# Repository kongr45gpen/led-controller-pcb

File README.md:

# led-controller-pcb

A PCB to control LEDs (up to 5 channels) using PWM, based on an Espressif ESP32-C6 development board.

Do you want to control your LEDs through Wi-Fi, Bluetooth or Zigbee, but you don't have 100€ lying around? This project is for you!
## Images

## Features

- 5 PWM **output channels**
- 5 **switch MOSFETS** (up to 8A)
- VIN **up to 28V**
- ESP32-C6 controllable through **USB, Wi-Fi, Bluetooth 5 (LE), IEEE 802.15.4**
- Support for RGB, RGBW, RGBWW/CW, WS2812B, and other configurations
- Control through MQTT, HomeAssistant
- **Non**-isolated input
- Fully open-source software and hardware
- 6.25 × 5 cm
- Not battle tested, so might stop working randomly

## Software

You can write your software using any framework you prefer. This board is built and will work out of the box for the [kongr45gpen/ledstripesp32](https://github.com/kongr45gpen/ledstripesp32) project specifically.

## Bill of Materials

This board is meant to function as a **controller** (generating low-power PWM signals from a network/wired input), as a **dimmer** (switching high-power LED lights on/off based on the input signal) or both.

The **controller** function is based on the [ESP32-C6-DevKitC-1](https://docs.espressif.com/projects/espressif-esp-dev-kits/en/latest/esp32c6/esp32-c6-devkitc-1/index.html) development board, but other ESP32 development boards should be also usable (not tested).

The **dimmer** function relies on a few MOSFETs to control the current flow from the output.

The rest of the components are mostly optional and slightly improve the functionality of the board (connectors, pull-down resistors etc). The user can choose whichever components they need and assemble the board to their preference. Many components (e.g. DC barrel jack, headers, passives) may be replaceable with cheaper generic alternatives.

An all-around configuration should cost ~20€, and adding a screen, voltage regulator and detachable headers should move the price up to ~35€.

A total project cost for a simple RGB led control system could be: 5m 5050 12V RGB LED strip (10€) + 12V 1A power supply (10€) + PCB (6€) + components (20€) = 46€.

With example parts and prices from Mouser:

| Ref | Part | Qu.| CONT. | DIM. | Description | Price |
| :-- | :--- | :------: | :--------: | :----: | ----------- | ----: |
| Brd1 | 4-pin I2C SSD1306 | 1 | ❓ | | Debugging info screen | 3€ |
| C1 | C 100nF 0603 (1608 metric) | 1 | | ✔️ | Decoupling capacitor | [0.1€](https://www.mouser.com/ProductDetail/581-04026D104KAT4A) |
| J1 | CUI PJ-063AH | 1 | | ❓ | VIN Barrel connector | [1.5€](https://www.mouser.com/ProductDetail/490-PJ-063AH) |
| J2 | Molex SL 171971-0002 | 1 | | ❓ | VIN Header connector | [0.8€](https://www.mouser.com/ProductDetail/Molex/171971-0002?qs=lc2O%252BfHJPVZiIVvtLkRJ0A%3D%3D) |
| J3 | Molex SL 171971-0007 | 1 | ❓ | ❓ | PWM input/output connector (5 pins + GND) | [1.5€](https://www.mouser.com/ProductDetail/Molex/171971-0007?qs=lc2O%252BfHJPVYTelce0YNW%252BQ%3D%3D) |
| J4 | 5mm 6-pin screw terminal | 1 | | ✔️ | Power output (5 pins + VDD) | [0.9€](https://www.mouser.com/ProductDetail/490-TB003-500-P06BE) |
| J5 | Molex SL 171971-0003 | 1 | ❓ | | Addressable LED output | [1.1€](https://www.mouser.com/ProductDetail/Molex/171971-0003?qs=lc2O%252BfHJPVYq9zLgxhm5jg%3D%3D) |
| LED1..5 | 0805 (2012 metric) LED | 5 | ❓ | ❓ | Indicator LEDs for PWM | [1.25€](https://www.mouser.com/ProductDetail/859-LTST-C170KFKT) |
| LED\_POWER1 | 0805 (2012 metric) LED | 1 | | ❓ | Indicator LED for VDD | [0.25€](https://www.mouser.com/ProductDetail/859-LTST-C170KFKT) |
| Q1..5 | IRLTS6342 (N-MOSFET) | 5 | | ✔️ | Control transistors (use as many as needed) | [1.7€](https://www.mouser.com/ProductDetail/Infineon-Technologies/IRLTS6342TRPBF?qs=8jYDHybYAxsDJhh9ct3B2Q%3D%3D) |
| R1..6 | R 15kΩ 0603 (1608 metric) | 6 | | ❓ | LED series resistors (use as many as needed) | [0.1€](https://www.mouser.com/ProductDetail/603-RC0603FR-0715KL) |
| Rpd1..5 | R 100kΩ 0603 (1608 metric) | 5 | ❓ | ❓ | Pull-down resistors to keep output off when disconnected | [0.1€](https://www.mouser.com/ProductDetail/603-RC0402FR-07100KL) |
| SW1 | PTS647SM70SMTR2LFS | 1 | ❓ | | ESP32 input switch | [0.2€](https://www.mouser.com/ProductDetail/CK/PTS647SM70SMTR2LFS?qs=PqoDHHvF64%252Bxl5nIb9IaOw%3D%3D) |
| U1 | ESP32-C6-DevKitC-1 | 1 | ✔️ | | ESP32 development kit | [8€](https://www.mouser.com/ProductDetail/356-ESP32C6DKC1N8) |
| VR1 | Wurth 1769405241 | 1 | ❓ | | Voltage regulator to provide 5V to ESP32 from VIN | [5€](https://www.mouser.com/ProductDetail/710-1769405241) |

### Extra Accessories

| Part | Quantity | CONTROLLER | DIMMER | Description | Price |
|---|:---:|:---:|:---:|---|---:|
| 4-pin header | 1 | ❓ |  | For screen (`Brd1`) | [0.7€](https://www.mouser.com/ProductDetail/200-CES10402TS) |
| 16-pin-header | 2 | ❓ | | For ESP32 (`U1`) | [5€](https://www.mouser.com/ProductDetail/200-CES11601TS) |
| Molex 14-60-0024 | 1 | | ❓ | Wire plug for `J2` | [0.4€](https://www.mouser.com/ProductDetail/538-14-60-0024) |
| Molex 14-60-0072 | 1 | ❓ | ❓ | Wire plug for `J3` | [1.5€](https://www.mouser.com/ProductDetail/538-14-60-0072) |
| Molex 14-56-7032 | 1 | ❓ | | Wire plug for `J5` | [0.7€](https://www.mouser.com/ProductDetail/538-14-56-7032) |

### Solder Bridges

Some solder bridges/solder jumpers may need to be soldered before any operation can take place.

| Ref | Pins | CONTROLLER | DIMMER | Description |
| :-- | :--: | :--------: | :----: | :---------- |
| JP1 | 3    |            | ✔️     | Controls the source of `VDD` for the LED power output. Bridge 2-1 to connect to `5V`. Bridge 2-3 to connect to `VIN` (J1, J2). |
| JP2 | 3    | ❓          |       | Controls the voltage source (typically 5V) for the addressable strip. Bridge 2-1 to connect to `5V`. Bridge 2-3 to connect to `VIN` (J1, J2). |
| JP3 | 2    |           | ✔️       | Bridge to connect power ground with digital ground. **Must** solder for proper operation.  |
| JP4 | 2    | ❓          |         | Bridge to connect VR1 output to 5V. Must solder to enable voltage regulation from VIN to ESP32 5V. Keep desoldered during debugging to prevent damaging your equipment.  |
| JPout1..5 | 2 | | ✔️ | Bridge to connect transistor outputs to output connector. You can alternatively wire a series resistor here for your output, if needed. |

### Example configurations

**All-in-one controller, from Wi-Fi to RGB LED strip**:
- C1, J1 to connect an external 12V power supply
- VR1 to convert the external 12V to 5V for the ESP32
- LED1..3, LED_POWER1, R1..3, R6 for debugging indicators
- Q1..3 as amplifiers
- Rpd1..3 to prevent lights from going up during boot
- J4 to screw LED strip wires
- U1 for control
- Bridge JP1 (2-3), JP3, JPout1..3. After uploading code, bridge JP4.
- BOM cost: **18€**

**Addressable strip controller with debugging screen**:
- No need for power input, as the ESP32 dev board already has USB-C connections
- U1 for control
- J5 connector to output addressable LED data
- J5 wire plug to solder on addressable LED
- Brd1 screen + 4-pin header to allow detaching it
- Bridge JP2 (2-1)
- BOM cost: **6€**

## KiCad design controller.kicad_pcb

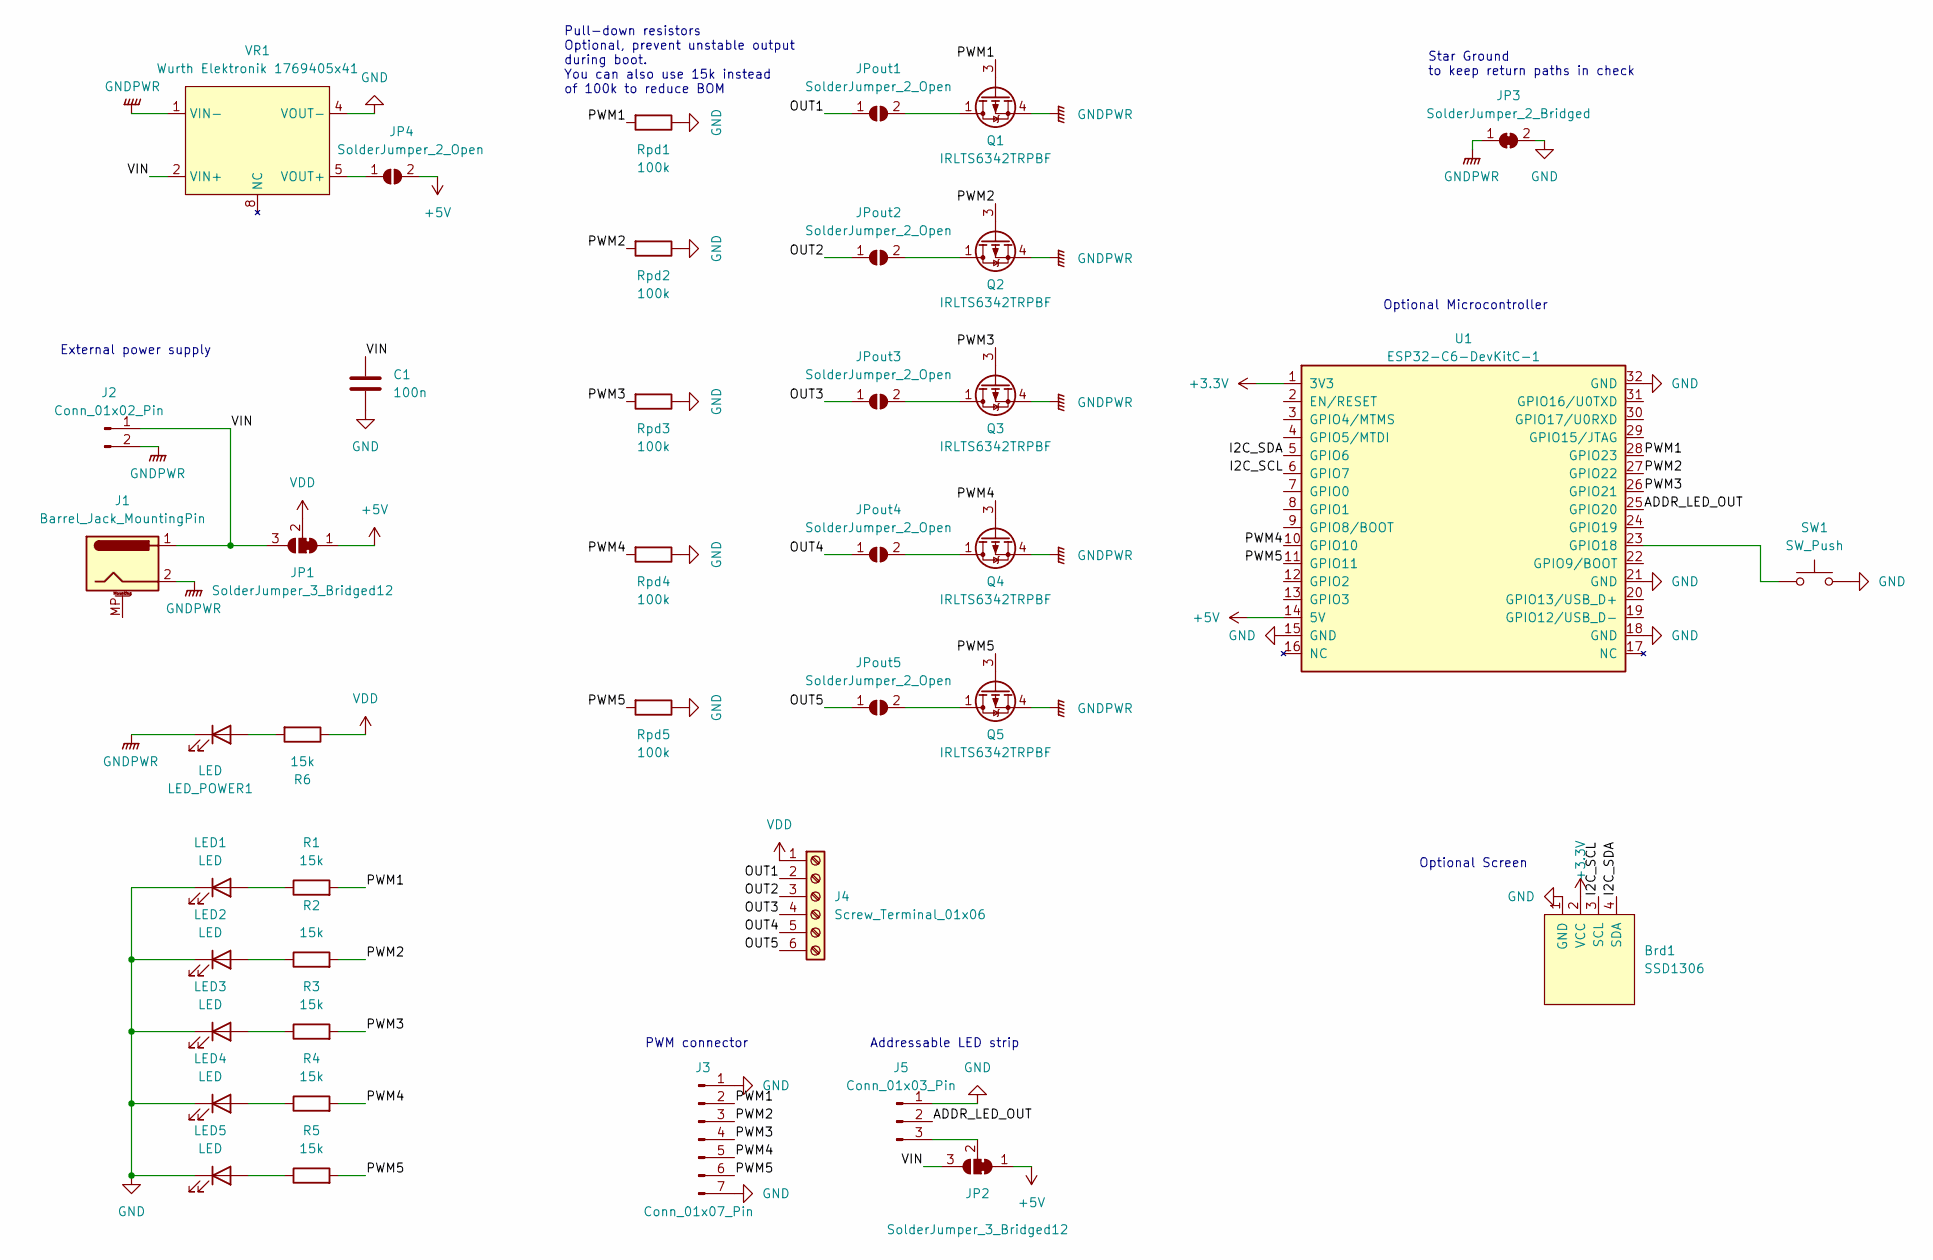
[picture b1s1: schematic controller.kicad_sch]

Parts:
Brd1: SSD1306; 128x64OLED
C1: 100n; C_0603_1608Metric_Pad1.08x0.95mm_HandSolder
J1: Barrel_Jack_MountingPin; BarrelJack_CUI_PJ-063AH_Horizontal_CircularHoles
J2: Conn_01x02_Pin; Molex_SL_171971-0002_1x02_P2.54mm_Vertical
J3: Conn_01x07_Pin; Molex_SL_171971-0007_1x07_P2.54mm_Vertical
J4: Screw_Terminal_01x06; TerminalBlock_RND_205-00005_1x06_P5.00mm_Horizontal
J5: Conn_01x03_Pin; Molex_SL_171971-0003_1x03_P2.54mm_Vertical
JP1, JP2: SolderJumper_3_Bridged12; SolderJumper-3_P1.3mm_Open_RoundedPad1.0x1.5mm_NumberLabels
JP3: SolderJumper_2_Bridged; SolderJumper-2_P1.3mm_Bridged2Bar_Pad1.0x1.5mm
JP4: SolderJumper_2_Open; SolderJumper-2_P1.3mm_Open_RoundedPad1.0x1.5mm
JPout1, JPout2, JPout3, JPout4, JPout5: SolderJumper_2_Open; SolderJumper-2_P1.3mm_Open_TrianglePad1.0x1.5mm
LED1, LED2, LED3, LED4, LED5: LED; LED_0805_2012Metric_Pad1.15x1.40mm_HandSolder
LED_POWER1: LED; LED_0805_2012Metric_Pad1.15x1.40mm_HandSolder
Q1, Q2, Q3, Q4, Q5: IRLTS6342TRPBF; TSOP-6_1.65x3.05mm_P0.95mm
R1, R2, R3, R4, R5, R6: 15k; R_0603_1608Metric_Pad0.98x0.95mm_HandSolder
Rpd1, Rpd2, Rpd3, Rpd4, Rpd5: 100k; R_0603_1608Metric_Pad0.98x0.95mm_HandSolder
SW1: SW_Push; SWITCH-4
U1: ESP32-C6-DevKitC-1
VR1: Wurth Elektronik 1769405x41; 1769405x41

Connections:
+3.3V: Brd1.2 (VCC), U1.1 (3V3)
+5V: JP1.1 (A), JP2.1 (A), JP4.2 (B), U1.14 (5V)
/ADDR_LED_OUT: J5.2, U1.25 (GPIO20)
/I2C_SCL: Brd1.3 (SCL), U1.6 (GPIO7)
/I2C_SDA: Brd1.4 (SDA), U1.5 (GPIO6)
/OUT1: J4.2, JPout1.1 (A)
/OUT2: J4.3, JPout2.1 (A)
/OUT3: J4.4, JPout3.1 (A)
/OUT4: J4.5, JPout4.1 (A)
/OUT5: J4.6, JPout5.1 (A)
/PWM1: J3.2, Q1.3 (G), R1.2, Rpd1.2, U1.28 (GPIO23)
/PWM2: J3.3, Q2.3 (G), R2.2, Rpd2.2, U1.27 (GPIO22)
/PWM3: J3.4, Q3.3 (G), R3.2, Rpd3.2, U1.26 (GPIO21)
/PWM4: J3.5, Q4.3 (G), R4.2, Rpd4.2, U1.10 (GPIO10)
/PWM5: J3.6, Q5.3 (G), R5.2, Rpd5.2, U1.11 (GPIO11)
/VIN: C1.1, J1.1, J2.1, JP1.3 (B), JP2.3 (B), VR1.2 (VIN+)
GND: Brd1.1 (GND), C1.2, J3.1, J3.7, J5.1, JP3.2 (B), LED1.1 (K), LED2.1 (K), LED3.1 (K), LED4.1 (K), LED5.1 (K), Rpd1.1, Rpd2.1, Rpd3.1, Rpd4.1, Rpd5.1, SW1.2, SW1.4, U1.15 (GND), U1.18 (GND), U1.21 (GND), U1.32 (GND), VR1.4 (VOUT-)
GNDPWR: J1.2, J2.2, JP3.1 (A), LED_POWER1.1 (K), Q1.4 (S), Q2.4 (S), Q3.4 (S), Q4.4 (S), Q5.4 (S), VR1.1 (VIN-)
unnamed: J5.3, JP2.2 (C)
unnamed: JP4.1 (A), VR1.5 (VOUT+)
unnamed: JPout1.2 (B), Q1.1 (D), Q1.2 (D), Q1.5 (D), Q1.6 (D)
unnamed: JPout2.2 (B), Q2.1 (D), Q2.2 (D), Q2.5 (D), Q2.6 (D)
unnamed: JPout3.2 (B), Q3.1 (D), Q3.2 (D), Q3.5 (D), Q3.6 (D)
unnamed: JPout4.2 (B), Q4.1 (D), Q4.2 (D), Q4.5 (D), Q4.6 (D)
unnamed: JPout5.2 (B), Q5.1 (D), Q5.2 (D), Q5.5 (D), Q5.6 (D)
unnamed: LED1.2 (A), R1.1
unnamed: LED2.2 (A), R2.1
unnamed: LED3.2 (A), R3.1
unnamed: LED4.2 (A), R4.1
unnamed: LED5.2 (A), R5.1
unnamed: LED_POWER1.2 (A), R6.2
unnamed: SW1.1, SW1.3, U1.23 (GPIO18)
VDD: J4.1, JP1.2 (C), R6.1

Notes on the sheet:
External power supply
Star Ground to keep return paths in check
Pull-down resistors Optional, prevent unstable output during boot. You can also use 15k instead of 100k to reduce BOM
Addressable LED strip
Optional Microcontroller
Optional Screen
PWM connector

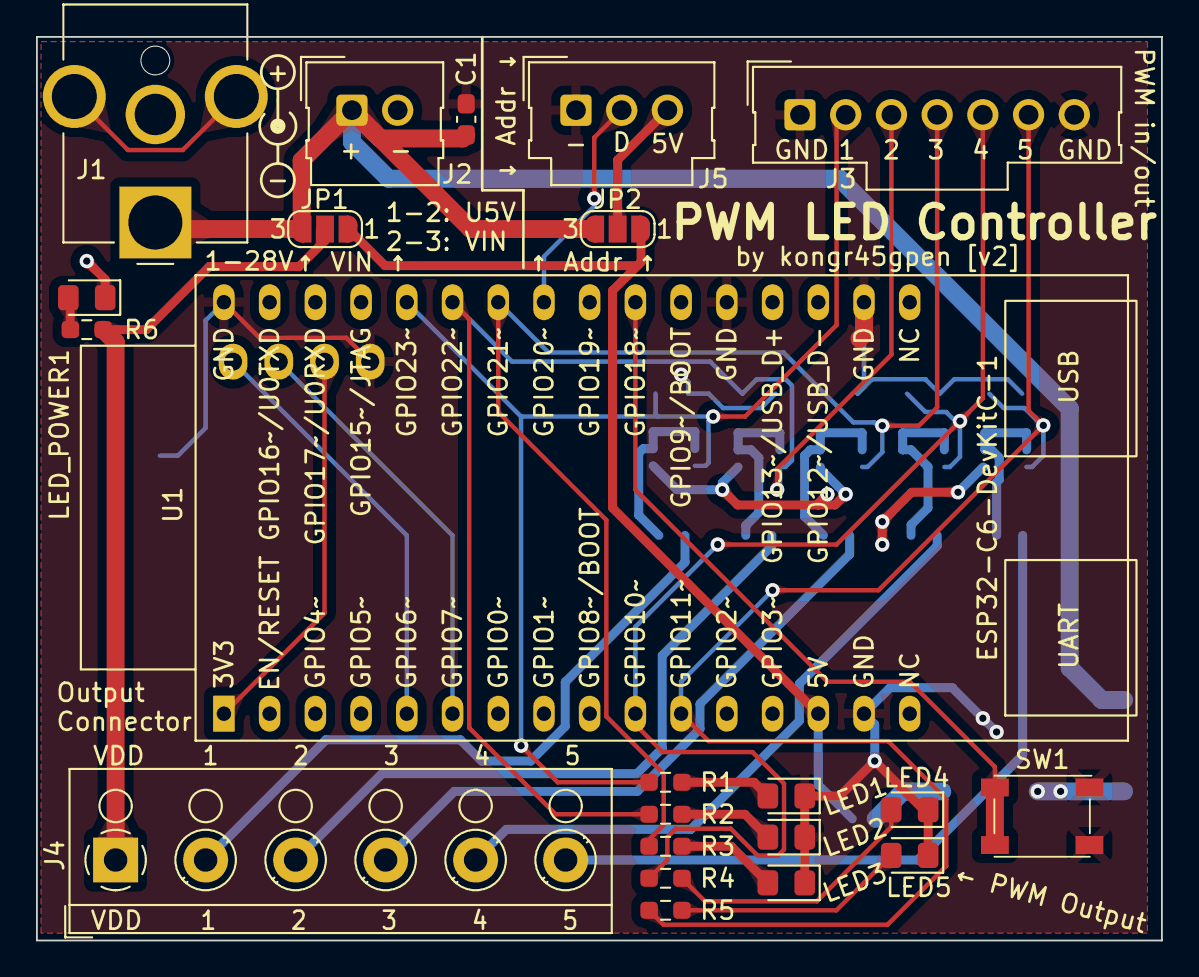
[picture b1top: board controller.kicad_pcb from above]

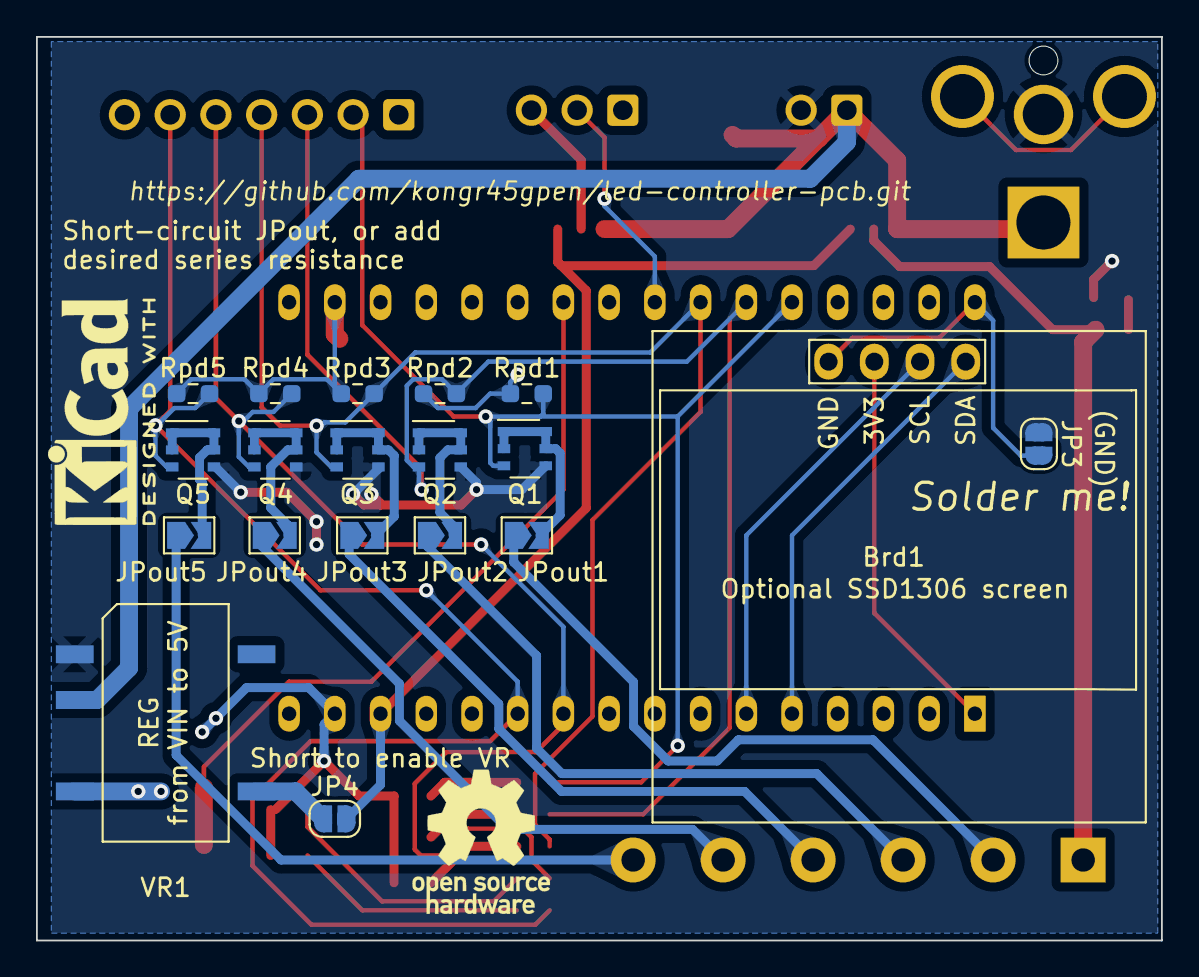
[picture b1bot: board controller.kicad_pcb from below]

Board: 2 copper layers, 62.5 x 50.2 mm, 41 parts (19 on the bottom side), 33 nets.

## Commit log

2023-07-09 Initial routing
2023-07-09 Beautify silkscreen
2023-07-09 Add button
2023-07-09 Add figures
2023-07-09 Remove useless file
2023-07-09 Add a LICENSE
2023-07-09 Increase board height to fit barrel jack pin
2023-07-10 Commit unsaved changes
2023-08-14 Updates for PCB v2
2023-08-14 Fix switch footprint
2023-08-14 Complete routing
2023-08-22 Add teardrops and beautify some traces
2023-08-26 Fill README with content
2023-08-26 Add some missing information about solder bridges
2023-08-26 Try to make text columns longer
